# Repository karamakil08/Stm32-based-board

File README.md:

# Stm32-based-board
This is a STM32F103C8T based board

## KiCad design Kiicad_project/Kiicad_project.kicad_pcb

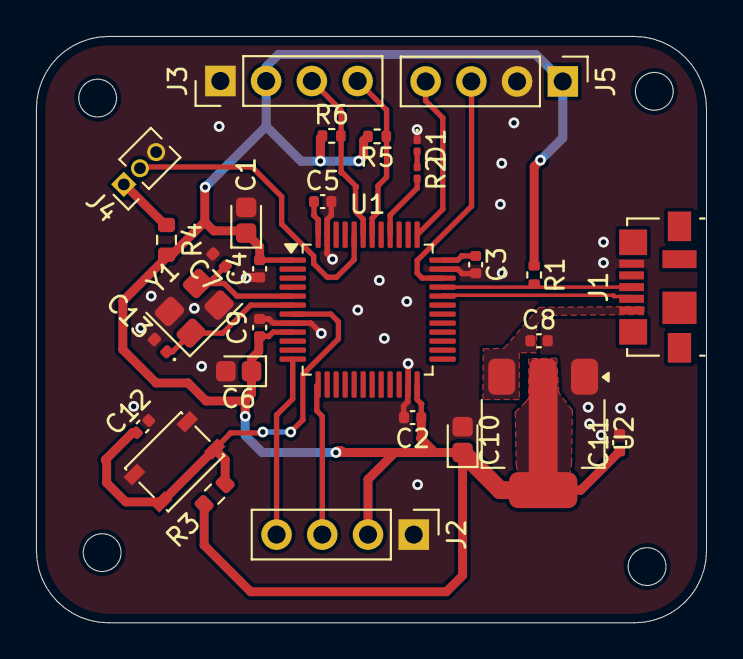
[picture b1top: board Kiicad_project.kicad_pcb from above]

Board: 4 copper layers, 37.2 x 32.6 mm, 33 parts (0 on the bottom side), 17 nets.

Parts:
C1: 10uF; CP_EIA-1608-08_AVX-J
C2, C3, C4, C5, C8, C9, C11, C12: 100nF; C_0402_1005Metric
C6: 4.7u; CP_EIA-1608-08_AVX-J
C7, C13: 10pF; D_0402_1005Metric
C10: 22uF; CP_EIA-1608-08_AVX-J
D1: Blue_LED; LED_0201_0603Metric
H1, H2, H3, H4: MountingHole; MountingHole_2.1mm
J1: USB_B_Micro; USB_Micro-B_Molex_47346-0001
J2: UART; PinHeader_1x04_P2.54mm_Vertical
J3: I2C; PinHeader_1x04_P2.54mm_Vertical
J4: Conn_01x03_Pin; PinHeader_1x03_P1.27mm_Vertical
J5: Conn_01x04_Pin; PinHeader_1x04_P2.54mm_Vertical
R1, R5, R6: 1k5; R_0402_1005Metric
R2: 220; R_0201_0603Metric
R3, R4: 10k; R_0603_1608Metric
SW1: SW_Push; SW_SPST_PTS810
U1: STM32F103C8Tx; LQFP-48_7x7mm_P0.5mm
U2: LT1117-3.3; SOT-223-3_TabPin2
Y1: Crystal_GND2; Crystal_SMD_3225-4Pin_3.2x2.5mm

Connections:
+3.3V: C1.1, C2.1, C3.1, C4.1, C5.1, C6.1, C9.1, C10.1, C11.1, J2.2, J3.2, J4.1, J5.1, R1.1, R3.1, R4.1, R4.2, R5.2, R6.1, U1.1 (VBAT), U1.9 (VDDA), U1.24 (VDD), U1.36 (VDD), U1.48 (VDD), U2.2 (VO)
/BOOT: J4.2, U1.44 (BOOT0)
/I2C_SCL: J3.4, R5.1, U1.42 (PB6)
/I2C_SDA: J3.3, R6.2, U1.43 (PB7)
/NRST: C12.1, R3.2, SW1.2, U1.7 (NRST)
/OSC_IN: C7.1, U1.5 (PD0), Y1.3
/OSC_OUT: C13.1, U1.6 (PD1), Y1.1
/SWCLK: J5.4, U1.37 (PA14)
/SWDIO: J5.3, U1.34 (PA13)
/UART_RX: J2.3, U1.13 (PA3)
/UART_TX: J2.4, U1.12 (PA2)
/USB_MICRO+: J1.3 (D+), R1.2, U1.33 (PA12)
/USB_MICRO-: J1.2 (D-), U1.32 (PA11)
GND: C1.2, C2.2, C3.2, C4.2, C5.2, C6.2, C7.2, C8.2, C9.2, C10.2, C11.2, C12.2, C13.2, D1.1 (K), J1.5 (GND), J2.1, J3.1, J4.3, J5.2, SW1.1, U1.8 (VSSA), U1.23 (VSS), U1.35 (VSS), U1.47 (VSS), U2.1 (GND), Y1.2, Y1.4
unnamed: D1.2 (A), R2.1
unnamed: R2.2, U1.40 (PB4)
VBUS: C8.1, J1.1 (VBUS), U2.3 (VI)
